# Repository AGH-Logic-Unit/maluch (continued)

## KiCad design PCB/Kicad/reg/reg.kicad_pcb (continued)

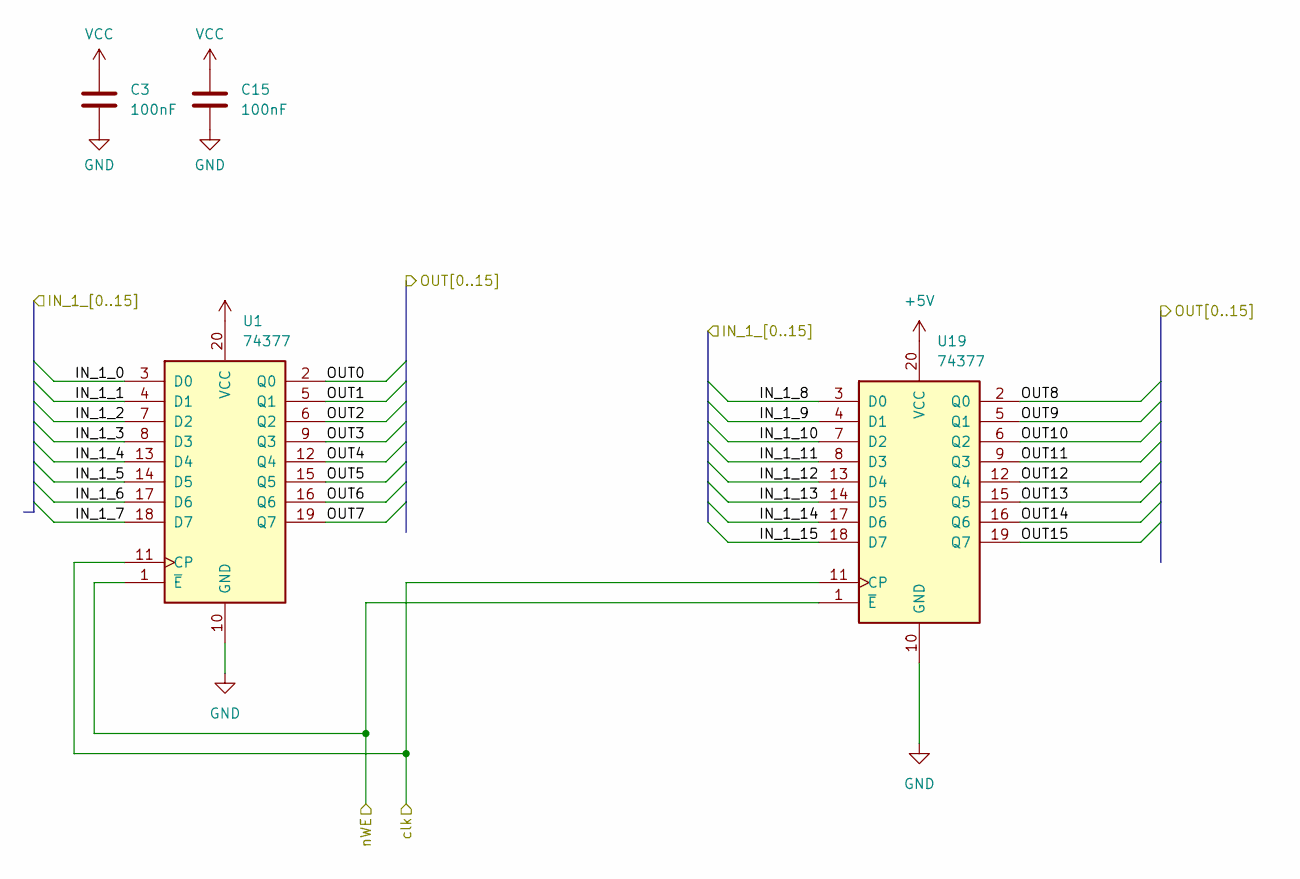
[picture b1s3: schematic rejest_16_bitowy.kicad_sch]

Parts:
C3, C15: 100nF; C_0402_1005Metric
U1, U19: 74377; SSOP-20_5.3x7.2mm_P0.65mm

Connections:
+5V: C3.1, C15.1, U1.20 (VCC), U19.20 (VCC); also elsewhere on the board
/16 bit buffor23/OUT0: U1.3 (D0); also elsewhere on the board
/16 bit buffor23/OUT1: U1.4 (D1); also elsewhere on the board
/16 bit buffor23/OUT2: U1.7 (D2); also elsewhere on the board
/16 bit buffor23/OUT3: U1.8 (D3); also elsewhere on the board
/16 bit buffor23/OUT4: U1.13 (D4); also elsewhere on the board
/16 bit buffor23/OUT5: U1.14 (D5); also elsewhere on the board
/16 bit buffor23/OUT6: U1.17 (D6); also elsewhere on the board
/16 bit buffor23/OUT7: U1.18 (D7); also elsewhere on the board
/16 bit buffor23/OUT8: U19.3 (D0); also elsewhere on the board
/16 bit buffor23/OUT9: U19.4 (D1); also elsewhere on the board
/16 bit buffor23/OUT10: U19.7 (D2); also elsewhere on the board
/16 bit buffor23/OUT11: U19.8 (D3); also elsewhere on the board
/16 bit buffor23/OUT12: U19.13 (D4); also elsewhere on the board
/16 bit buffor23/OUT13: U19.14 (D5); also elsewhere on the board
/16 bit buffor23/OUT14: U19.17 (D6); also elsewhere on the board
/16 bit buffor23/OUT15: U19.18 (D7); also elsewhere on the board
/16 bit register18/nWE: U1.1 (~E), U19.1 (~E); also elsewhere on the board
/clk: U1.11 (CP), U19.11 (CP); also elsewhere on the board
/mask_saved0: U1.2 (Q0); also elsewhere on the board
/mask_saved1: U1.5 (Q1); also elsewhere on the board
/mask_saved2: U1.6 (Q2); also elsewhere on the board
/mask_saved3: U1.9 (Q3); also elsewhere on the board
/mask_saved4: U1.12 (Q4); also elsewhere on the board
/mask_saved5: U1.15 (Q5); also elsewhere on the board
/mask_saved6: U1.16 (Q6); also elsewhere on the board
/mask_saved7: U1.19 (Q7); also elsewhere on the board
/mask_saved8: U19.2 (Q0); also elsewhere on the board
/mask_saved9: U19.5 (Q1); also elsewhere on the board
/mask_saved10: U19.6 (Q2); also elsewhere on the board
/mask_saved11: U19.9 (Q3); also elsewhere on the board
/mask_saved12: U19.12 (Q4); also elsewhere on the board
/mask_saved13: U19.15 (Q5); also elsewhere on the board
/mask_saved14: U19.16 (Q6); also elsewhere on the board
/mask_saved15: U19.19 (Q7); also elsewhere on the board
GND: C3.2, C15.2, U1.10 (GND), U19.10 (GND); also elsewhere on the board

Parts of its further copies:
C4, C16, C17, C18, C19, C20, C21, C22, C23, C24, C25, C26, C27, C28, C29, C30, C31, C32, C33, C34, C35, C36, C37, C38, C39, C40, C41, C42, C43, C44, C45, C46: 100nF; C_0402_1005Metric
U14, U18, U20, U23, U24, U25, U26, U27, U28, U31, U32, U33, U34, U35, U36, U37, U38, U39, U40, U41, U42, U43, U44, U45, U46, U47, U48, U49, U50, U51, U52, U53: 74377; SSOP-20_5.3x7.2mm_P0.65mm

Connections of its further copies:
+5V: C4.1, C16.1, C17.1, C18.1, C19.1, C20.1, C21.1, C22.1, C23.1, C24.1, C25.1, C26.1, C27.1, C28.1, C29.1, C30.1, C31.1, C32.1, C33.1, C34.1, C35.1, C36.1, C37.1, C38.1, C39.1, C40.1, C41.1, C42.1, C43.1, C44.1, C45.1, C46.1, U14.20 (VCC), U18.20 (VCC), U20.20 (VCC), U23.20 (VCC), U24.20 (VCC), U25.20 (VCC), U26.20 (VCC), U27.20 (VCC), U28.20 (VCC), U31.20 (VCC), U32.20 (VCC), U33.20 (VCC), U34.20 (VCC), U35.20 (VCC), U36.20 (VCC), U37.20 (VCC), U38.20 (VCC), U39.20 (VCC), U40.20 (VCC), U41.20 (VCC), U42.20 (VCC), U43.20 (VCC), U44.20 (VCC), U45.20 (VCC), U46.20 (VCC), U47.20 (VCC), U48.20 (VCC), U49.20 (VCC), U50.20 (VCC), U51.20 (VCC), U52.20 (VCC), U53.20 (VCC); also elsewhere on the board
/16 bit buffor25/OUT0: U14.3 (D0); also elsewhere on the board
/16 bit buffor25/OUT1: U14.4 (D1); also elsewhere on the board
/16 bit buffor25/OUT2: U14.7 (D2); also elsewhere on the board
/16 bit buffor25/OUT3: U14.8 (D3); also elsewhere on the board
/16 bit buffor25/OUT4: U14.13 (D4); also elsewhere on the board
/16 bit buffor25/OUT5: U14.14 (D5); also elsewhere on the board
/16 bit buffor25/OUT6: U14.17 (D6); also elsewhere on the board
/16 bit buffor25/OUT7: U14.18 (D7); also elsewhere on the board
/16 bit buffor25/OUT8: U20.3 (D0); also elsewhere on the board
/16 bit buffor25/OUT9: U20.4 (D1); also elsewhere on the board
/16 bit buffor25/OUT10: U20.7 (D2); also elsewhere on the board
/16 bit buffor25/OUT11: U20.8 (D3); also elsewhere on the board
/16 bit buffor25/OUT12: U20.13 (D4); also elsewhere on the board
/16 bit buffor25/OUT13: U20.14 (D5); also elsewhere on the board
/16 bit buffor25/OUT14: U20.17 (D6); also elsewhere on the board
/16 bit buffor25/OUT15: U20.18 (D7); also elsewhere on the board
/16 bit buffor28/IN_1_0: U18.2 (Q0); also elsewhere on the board
/16 bit buffor28/IN_1_1: U18.5 (Q1); also elsewhere on the board
/16 bit buffor28/IN_1_2: U18.6 (Q2); also elsewhere on the board
/16 bit buffor28/IN_1_3: U18.9 (Q3); also elsewhere on the board
/16 bit buffor28/IN_1_4: U18.12 (Q4); also elsewhere on the board
/16 bit buffor28/IN_1_5: U18.15 (Q5); also elsewhere on the board
/16 bit buffor28/IN_1_6: U18.16 (Q6); also elsewhere on the board
/16 bit buffor28/IN_1_7: U18.19 (Q7); also elsewhere on the board
/16 bit buffor28/IN_1_8: U23.2 (Q0); also elsewhere on the board
/16 bit buffor28/IN_1_9: U23.5 (Q1); also elsewhere on the board
/16 bit buffor28/IN_1_10: U23.6 (Q2); also elsewhere on the board
/16 bit buffor28/IN_1_11: U23.9 (Q3); also elsewhere on the board
/16 bit buffor28/IN_1_12: U23.12 (Q4); also elsewhere on the board
/16 bit buffor28/IN_1_13: U23.15 (Q5); also elsewhere on the board
/16 bit buffor28/IN_1_14: U23.16 (Q6); also elsewhere on the board
/16 bit buffor28/IN_1_15: U23.19 (Q7); also elsewhere on the board
/16 bit buffor29/IN_1_0: U31.2 (Q0); also elsewhere on the board
/16 bit buffor29/IN_1_1: U31.5 (Q1); also elsewhere on the board
/16 bit buffor29/IN_1_2: U31.6 (Q2); also elsewhere on the board
/16 bit buffor29/IN_1_3: U31.9 (Q3); also elsewhere on the board
/16 bit buffor29/IN_1_4: U31.12 (Q4); also elsewhere on the board
/16 bit buffor29/IN_1_5: U31.15 (Q5); also elsewhere on the board
/16 bit buffor29/IN_1_6: U31.16 (Q6); also elsewhere on the board
/16 bit buffor29/IN_1_7: U31.19 (Q7); also elsewhere on the board
/16 bit buffor29/IN_1_8: U24.2 (Q0); also elsewhere on the board
/16 bit buffor29/IN_1_9: U24.5 (Q1); also elsewhere on the board
/16 bit buffor29/IN_1_10: U24.6 (Q2); also elsewhere on the board
/16 bit buffor29/IN_1_11: U24.9 (Q3); also elsewhere on the board
/16 bit buffor29/IN_1_12: U24.12 (Q4); also elsewhere on the board
/16 bit buffor29/IN_1_13: U24.15 (Q5); also elsewhere on the board
/16 bit buffor29/IN_1_14: U24.16 (Q6); also elsewhere on the board
/16 bit buffor29/IN_1_15: U24.19 (Q7); also elsewhere on the board
/16 bit buffor30/IN_1_0: U32.2 (Q0); also elsewhere on the board
/16 bit buffor30/IN_1_1: U32.5 (Q1); also elsewhere on the board
/16 bit buffor30/IN_1_2: U32.6 (Q2); also elsewhere on the board
/16 bit buffor30/IN_1_3: U32.9 (Q3); also elsewhere on the board
/16 bit buffor30/IN_1_4: U32.12 (Q4); also elsewhere on the board
/16 bit buffor30/IN_1_5: U32.15 (Q5); also elsewhere on the board
/16 bit buffor30/IN_1_6: U32.16 (Q6); also elsewhere on the board
/16 bit buffor30/IN_1_7: U32.19 (Q7); also elsewhere on the board
/16 bit buffor30/IN_1_8: U25.2 (Q0); also elsewhere on the board
/16 bit buffor30/IN_1_9: U25.5 (Q1); also elsewhere on the board
/16 bit buffor30/IN_1_10: U25.6 (Q2); also elsewhere on the board
/16 bit buffor30/IN_1_11: U25.9 (Q3); also elsewhere on the board
/16 bit buffor30/IN_1_12: U25.12 (Q4); also elsewhere on the board
/16 bit buffor30/IN_1_13: U25.15 (Q5); also elsewhere on the board
/16 bit buffor30/IN_1_14: U25.16 (Q6); also elsewhere on the board
/16 bit buffor30/IN_1_15: U25.19 (Q7); also elsewhere on the board
/16 bit buffor31/IN_1_0: U42.2 (Q0); also elsewhere on the board
/16 bit buffor31/IN_1_1: U42.5 (Q1); also elsewhere on the board
/16 bit buffor31/IN_1_2: U42.6 (Q2); also elsewhere on the board
/16 bit buffor31/IN_1_3: U42.9 (Q3); also elsewhere on the board
/16 bit buffor31/IN_1_4: U42.12 (Q4); also elsewhere on the board
/16 bit buffor31/IN_1_5: U42.15 (Q5); also elsewhere on the board
/16 bit buffor31/IN_1_6: U42.16 (Q6); also elsewhere on the board
/16 bit buffor31/IN_1_7: U42.19 (Q7); also elsewhere on the board
/16 bit buffor31/IN_1_8: U39.2 (Q0); also elsewhere on the board
/16 bit buffor31/IN_1_9: U39.5 (Q1); also elsewhere on the board
/16 bit buffor31/IN_1_10: U39.6 (Q2); also elsewhere on the board
/16 bit buffor31/IN_1_11: U39.9 (Q3); also elsewhere on the board
/16 bit buffor31/IN_1_12: U39.12 (Q4); also elsewhere on the board
/16 bit buffor31/IN_1_13: U39.15 (Q5); also elsewhere on the board
/16 bit buffor31/IN_1_14: U39.16 (Q6); also elsewhere on the board
/16 bit buffor31/IN_1_15: U39.19 (Q7); also elsewhere on the board
/16 bit buffor32/IN_1_0: U33.2 (Q0); also elsewhere on the board
/16 bit buffor32/IN_1_1: U33.5 (Q1); also elsewhere on the board
/16 bit buffor32/IN_1_2: U33.6 (Q2); also elsewhere on the board
/16 bit buffor32/IN_1_3: U33.9 (Q3); also elsewhere on the board
/16 bit buffor32/IN_1_4: U33.12 (Q4); also elsewhere on the board
/16 bit buffor32/IN_1_5: U33.15 (Q5); also elsewhere on the board
/16 bit buffor32/IN_1_6: U33.16 (Q6); also elsewhere on the board
/16 bit buffor32/IN_1_7: U33.19 (Q7); also elsewhere on the board
/16 bit buffor32/IN_1_8: U26.2 (Q0); also elsewhere on the board
/16 bit buffor32/IN_1_9: U26.5 (Q1); also elsewhere on the board
/16 bit buffor32/IN_1_10: U26.6 (Q2); also elsewhere on the board
/16 bit buffor32/IN_1_11: U26.9 (Q3); also elsewhere on the board
/16 bit buffor32/IN_1_12: U26.12 (Q4); also elsewhere on the board
/16 bit buffor32/IN_1_13: U26.15 (Q5); also elsewhere on the board
/16 bit buffor32/IN_1_14: U26.16 (Q6); also elsewhere on the board
/16 bit buffor32/IN_1_15: U26.19 (Q7); also elsewhere on the board
/16 bit buffor33/IN_1_0: U34.2 (Q0); also elsewhere on the board
/16 bit buffor33/IN_1_1: U34.5 (Q1); also elsewhere on the board
/16 bit buffor33/IN_1_2: U34.6 (Q2); also elsewhere on the board
/16 bit buffor33/IN_1_3: U34.9 (Q3); also elsewhere on the board
/16 bit buffor33/IN_1_4: U34.12 (Q4); also elsewhere on the board
/16 bit buffor33/IN_1_5: U34.15 (Q5); also elsewhere on the board
/16 bit buffor33/IN_1_6: U34.16 (Q6); also elsewhere on the board
/16 bit buffor33/IN_1_7: U34.19 (Q7); also elsewhere on the board
/16 bit buffor33/IN_1_8: U27.2 (Q0); also elsewhere on the board
/16 bit buffor33/IN_1_9: U27.5 (Q1); also elsewhere on the board
/16 bit buffor33/IN_1_10: U27.6 (Q2); also elsewhere on the board
/16 bit buffor33/IN_1_11: U27.9 (Q3); also elsewhere on the board
/16 bit buffor33/IN_1_12: U27.12 (Q4); also elsewhere on the board
/16 bit buffor33/IN_1_13: U27.15 (Q5); also elsewhere on the board
/16 bit buffor33/IN_1_14: U27.16 (Q6); also elsewhere on the board
/16 bit buffor33/IN_1_15: U27.19 (Q7); also elsewhere on the board
/16 bit buffor34/IN_1_0: U37.2 (Q0); also elsewhere on the board
/16 bit buffor34/IN_1_1: U37.5 (Q1); also elsewhere on the board
/16 bit buffor34/IN_1_2: U37.6 (Q2); also elsewhere on the board
/16 bit buffor34/IN_1_3: U37.9 (Q3); also elsewhere on the board
/16 bit buffor34/IN_1_4: U37.12 (Q4); also elsewhere on the board
/16 bit buffor34/IN_1_5: U37.15 (Q5); also elsewhere on the board
/16 bit buffor34/IN_1_6: U37.16 (Q6); also elsewhere on the board
/16 bit buffor34/IN_1_7: U37.19 (Q7); also elsewhere on the board
/16 bit buffor34/IN_1_8: U28.2 (Q0); also elsewhere on the board
/16 bit buffor34/IN_1_9: U28.5 (Q1); also elsewhere on the board
/16 bit buffor34/IN_1_10: U28.6 (Q2); also elsewhere on the board
/16 bit buffor34/IN_1_11: U28.9 (Q3); also elsewhere on the board
/16 bit buffor34/IN_1_12: U28.12 (Q4); also elsewhere on the board
/16 bit buffor34/IN_1_13: U28.15 (Q5); also elsewhere on the board
/16 bit buffor34/IN_1_14: U28.16 (Q6); also elsewhere on the board
/16 bit buffor34/IN_1_15: U28.19 (Q7); also elsewhere on the board
/16 bit buffor35/IN_1_0: U38.2 (Q0); also elsewhere on the board
/16 bit buffor35/IN_1_1: U38.5 (Q1); also elsewhere on the board
/16 bit buffor35/IN_1_2: U38.6 (Q2); also elsewhere on the board
/16 bit buffor35/IN_1_3: U38.9 (Q3); also elsewhere on the board
/16 bit buffor35/IN_1_4: U38.12 (Q4); also elsewhere on the board
/16 bit buffor35/IN_1_5: U38.15 (Q5); also elsewhere on the board
/16 bit buffor35/IN_1_6: U38.16 (Q6); also elsewhere on the board
/16 bit buffor35/IN_1_7: U38.19 (Q7); also elsewhere on the board
/16 bit buffor35/IN_1_8: U35.2 (Q0); also elsewhere on the board
/16 bit buffor35/IN_1_9: U35.5 (Q1); also elsewhere on the board
/16 bit buffor35/IN_1_10: U35.6 (Q2); also elsewhere on the board
/16 bit buffor35/IN_1_11: U35.9 (Q3); also elsewhere on the board
/16 bit buffor35/IN_1_12: U35.12 (Q4); also elsewhere on the board
/16 bit buffor35/IN_1_13: U35.15 (Q5); also elsewhere on the board
/16 bit buffor35/IN_1_14: U35.16 (Q6); also elsewhere on the board
/16 bit buffor35/IN_1_15: U35.19 (Q7); also elsewhere on the board
/16 bit buffor36/IN_1_0: U41.2 (Q0); also elsewhere on the board
/16 bit buffor36/IN_1_1: U41.5 (Q1); also elsewhere on the board
/16 bit buffor36/IN_1_2: U41.6 (Q2); also elsewhere on the board
/16 bit buffor36/IN_1_3: U41.9 (Q3); also elsewhere on the board
/16 bit buffor36/IN_1_4: U41.12 (Q4); also elsewhere on the board
/16 bit buffor36/IN_1_5: U41.15 (Q5); also elsewhere on the board
/16 bit buffor36/IN_1_6: U41.16 (Q6); also elsewhere on the board
/16 bit buffor36/IN_1_7: U41.19 (Q7); also elsewhere on the board
/16 bit buffor36/IN_1_8: U36.2 (Q0); also elsewhere on the board
/16 bit buffor36/IN_1_9: U36.5 (Q1); also elsewhere on the board
/16 bit buffor36/IN_1_10: U36.6 (Q2); also elsewhere on the board
/16 bit buffor36/IN_1_11: U36.9 (Q3); also elsewhere on the board
/16 bit buffor36/IN_1_12: U36.12 (Q4); also elsewhere on the board
/16 bit buffor36/IN_1_13: U36.15 (Q5); also elsewhere on the board
/16 bit buffor36/IN_1_14: U36.16 (Q6); also elsewhere on the board
/16 bit buffor36/IN_1_15: U36.19 (Q7); also elsewhere on the board
/16 bit buffor37/IN_1_0: U45.2 (Q0); also elsewhere on the board
/16 bit buffor37/IN_1_1: U45.5 (Q1); also elsewhere on the board
/16 bit buffor37/IN_1_2: U45.6 (Q2); also elsewhere on the board
/16 bit buffor37/IN_1_3: U45.9 (Q3); also elsewhere on the board
/16 bit buffor37/IN_1_4: U45.12 (Q4); also elsewhere on the board
/16 bit buffor37/IN_1_5: U45.15 (Q5); also elsewhere on the board
/16 bit buffor37/IN_1_6: U45.16 (Q6); also elsewhere on the board
/16 bit buffor37/IN_1_7: U45.19 (Q7); also elsewhere on the board
/16 bit buffor37/IN_1_8: U40.2 (Q0); also elsewhere on the board
/16 bit buffor37/IN_1_9: U40.5 (Q1); also elsewhere on the board
/16 bit buffor37/IN_1_10: U40.6 (Q2); also elsewhere on the board
/16 bit buffor37/IN_1_11: U40.9 (Q3); also elsewhere on the board
/16 bit buffor37/IN_1_12: U40.12 (Q4); also elsewhere on the board
/16 bit buffor37/IN_1_13: U40.15 (Q5); also elsewhere on the board
/16 bit buffor37/IN_1_14: U40.16 (Q6); also elsewhere on the board
/16 bit buffor37/IN_1_15: U40.19 (Q7); also elsewhere on the board
/16 bit buffor38/IN_1_0: U46.2 (Q0); also elsewhere on the board
/16 bit buffor38/IN_1_1: U46.5 (Q1); also elsewhere on the board
/16 bit buffor38/IN_1_2: U46.6 (Q2); also elsewhere on the board
/16 bit buffor38/IN_1_3: U46.9 (Q3); also elsewhere on the board
/16 bit buffor38/IN_1_4: U46.12 (Q4); also elsewhere on the board
/16 bit buffor38/IN_1_5: U46.15 (Q5); also elsewhere on the board
/16 bit buffor38/IN_1_6: U46.16 (Q6); also elsewhere on the board
/16 bit buffor38/IN_1_7: U46.19 (Q7); also elsewhere on the board
/16 bit buffor38/IN_1_8: U43.2 (Q0); also elsewhere on the board
/16 bit buffor38/IN_1_9: U43.5 (Q1); also elsewhere on the board
/16 bit buffor38/IN_1_10: U43.6 (Q2); also elsewhere on the board
/16 bit buffor38/IN_1_11: U43.9 (Q3); also elsewhere on the board
/16 bit buffor38/IN_1_12: U43.12 (Q4); also elsewhere on the board
/16 bit buffor38/IN_1_13: U43.15 (Q5); also elsewhere on the board
/16 bit buffor38/IN_1_14: U43.16 (Q6); also elsewhere on the board
/16 bit buffor38/IN_1_15: U43.19 (Q7); also elsewhere on the board
/16 bit buffor39/IN_1_0: U50.2 (Q0); also elsewhere on the board
/16 bit buffor39/IN_1_1: U50.5 (Q1); also elsewhere on the board
/16 bit buffor39/IN_1_2: U50.6 (Q2); also elsewhere on the board
/16 bit buffor39/IN_1_3: U50.9 (Q3); also elsewhere on the board
/16 bit buffor39/IN_1_4: U50.12 (Q4); also elsewhere on the board
/16 bit buffor39/IN_1_5: U50.15 (Q5); also elsewhere on the board
/16 bit buffor39/IN_1_6: U50.16 (Q6); also elsewhere on the board
/16 bit buffor39/IN_1_7: U50.19 (Q7); also elsewhere on the board
/16 bit buffor39/IN_1_8: U47.2 (Q0); also elsewhere on the board
/16 bit buffor39/IN_1_9: U47.5 (Q1); also elsewhere on the board
/16 bit buffor39/IN_1_10: U47.6 (Q2); also elsewhere on the board
/16 bit buffor39/IN_1_11: U47.9 (Q3); also elsewhere on the board
/16 bit buffor39/IN_1_12: U47.12 (Q4); also elsewhere on the board
/16 bit buffor39/IN_1_13: U47.15 (Q5); also elsewhere on the board
/16 bit buffor39/IN_1_14: U47.16 (Q6); also elsewhere on the board
/16 bit buffor39/IN_1_15: U47.19 (Q7); also elsewhere on the board
/16 bit buffor40/IN_1_0: U49.2 (Q0); also elsewhere on the board
/16 bit buffor40/IN_1_1: U49.5 (Q1); also elsewhere on the board
/16 bit buffor40/IN_1_2: U49.6 (Q2); also elsewhere on the board
/16 bit buffor40/IN_1_3: U49.9 (Q3); also elsewhere on the board
/16 bit buffor40/IN_1_4: U49.12 (Q4); also elsewhere on the board
/16 bit buffor40/IN_1_5: U49.15 (Q5); also elsewhere on the board
/16 bit buffor40/IN_1_6: U49.16 (Q6); also elsewhere on the board
/16 bit buffor40/IN_1_7: U49.19 (Q7); also elsewhere on the board
/16 bit buffor40/IN_1_8: U44.2 (Q0); also elsewhere on the board
/16 bit buffor40/IN_1_9: U44.5 (Q1); also elsewhere on the board
/16 bit buffor40/IN_1_10: U44.6 (Q2); also elsewhere on the board
/16 bit buffor40/IN_1_11: U44.9 (Q3); also elsewhere on the board
/16 bit buffor40/IN_1_12: U44.12 (Q4); also elsewhere on the board
/16 bit buffor40/IN_1_13: U44.15 (Q5); also elsewhere on the board
/16 bit buffor40/IN_1_14: U44.16 (Q6); also elsewhere on the board
/16 bit buffor40/IN_1_15: U44.19 (Q7); also elsewhere on the board
/16 bit buffor41/IN_1_0: U52.2 (Q0); also elsewhere on the board
/16 bit buffor41/IN_1_1: U52.5 (Q1); also elsewhere on the board
/16 bit buffor41/IN_1_2: U52.6 (Q2); also elsewhere on the board
/16 bit buffor41/IN_1_3: U52.9 (Q3); also elsewhere on the board
/16 bit buffor41/IN_1_4: U52.12 (Q4); also elsewhere on the board
/16 bit buffor41/IN_1_5: U52.15 (Q5); also elsewhere on the board
/16 bit buffor41/IN_1_6: U52.16 (Q6); also elsewhere on the board
/16 bit buffor41/IN_1_7: U52.19 (Q7); also elsewhere on the board
/16 bit buffor41/IN_1_8: U48.2 (Q0); also elsewhere on the board
/16 bit buffor41/IN_1_9: U48.5 (Q1); also elsewhere on the board
/16 bit buffor41/IN_1_10: U48.6 (Q2); also elsewhere on the board
/16 bit buffor41/IN_1_11: U48.9 (Q3); also elsewhere on the board
/16 bit buffor41/IN_1_12: U48.12 (Q4); also elsewhere on the board
/16 bit buffor41/IN_1_13: U48.15 (Q5); also elsewhere on the board
/16 bit buffor41/IN_1_14: U48.16 (Q6); also elsewhere on the board
/16 bit buffor41/IN_1_15: U48.19 (Q7); also elsewhere on the board
/16 bit register17/nWE: U14.1 (~E), U20.1 (~E); also elsewhere on the board
/IO0: U53.3 (D0); also elsewhere on the board
/IO1: U53.4 (D1); also elsewhere on the board
/IO2: U53.7 (D2); also elsewhere on the board
/IO3: U53.8 (D3); also elsewhere on the board
/IO4: U53.13 (D4); also elsewhere on the board
/IO5: U53.14 (D5); also elsewhere on the board
/IO6: U53.17 (D6); also elsewhere on the board
/IO7: U53.18 (D7); also elsewhere on the board
/IO8: U51.3 (D0); also elsewhere on the board
/IO9: U51.4 (D1); also elsewhere on the board
/IO10: U51.7 (D2); also elsewhere on the board
/IO11: U51.8 (D3); also elsewhere on the board
/IO12: U51.13 (D4); also elsewhere on the board
/IO13: U51.14 (D5); also elsewhere on the board
/IO14: U51.17 (D6); also elsewhere on the board
/IO15: U51.18 (D7); also elsewhere on the board
/OUT_1_2: U18.1 (~E), U23.1 (~E); also elsewhere on the board
/OUT_1_3: U24.1 (~E), U31.1 (~E); also elsewhere on the board
/OUT_1_4: U25.1 (~E), U32.1 (~E); also elsewhere on the board
/OUT_1_5: U39.1 (~E), U42.1 (~E); also elsewhere on the board
/OUT_1_6: U26.1 (~E), U33.1 (~E); also elsewhere on the board
/OUT_1_7: U27.1 (~E), U34.1 (~E); also elsewhere on the board
/OUT_1_8: U28.1 (~E), U37.1 (~E); also elsewhere on the board
/OUT_1_9: U35.1 (~E), U38.1 (~E); also elsewhere on the board
/OUT_1_10: U36.1 (~E), U41.1 (~E); also elsewhere on the board
/OUT_1_11: U40.1 (~E), U45.1 (~E); also elsewhere on the board
/OUT_1_12: U43.1 (~E), U46.1 (~E); also elsewhere on the board
/OUT_1_13: U44.1 (~E), U49.1 (~E); also elsewhere on the board
/OUT_1_14: U47.1 (~E), U50.1 (~E); also elsewhere on the board
/OUT_1_15: U48.1 (~E), U52.1 (~E); also elsewhere on the board
/OUT_5_0: U53.2 (Q0); also elsewhere on the board
/OUT_5_1: U53.5 (Q1); also elsewhere on the board
/OUT_5_2: U53.6 (Q2); also elsewhere on the board
/OUT_5_3: U53.9 (Q3); also elsewhere on the board
/OUT_5_4: U53.12 (Q4); also elsewhere on the board
/OUT_5_5: U53.15 (Q5); also elsewhere on the board
/OUT_5_6: U53.16 (Q6); also elsewhere on the board
/OUT_5_7: U53.19 (Q7); also elsewhere on the board
/OUT_5_8: U51.2 (Q0); also elsewhere on the board
/OUT_5_9: U51.5 (Q1); also elsewhere on the board
/OUT_5_10: U51.6 (Q2); also elsewhere on the board
/OUT_5_11: U51.9 (Q3); also elsewhere on the board
/OUT_5_12: U51.12 (Q4); also elsewhere on the board
/OUT_5_13: U51.15 (Q5); also elsewhere on the board
/OUT_5_14: U51.16 (Q6); also elsewhere on the board
/OUT_5_15: U51.19 (Q7); also elsewhere on the board
/clk: U14.11 (CP), U18.11 (CP), U20.11 (CP), U23.11 (CP), U24.11 (CP), U25.11 (CP), U26.11 (CP), U27.11 (CP), U28.11 (CP), U31.11 (CP), U32.11 (CP), U33.11 (CP), U34.11 (CP), U35.11 (CP), U36.11 (CP), U37.11 (CP), U38.11 (CP), U39.11 (CP), U40.11 (CP), U41.11 (CP), U42.11 (CP), U43.11 (CP), U44.11 (CP), U45.11 (CP), U46.11 (CP), U47.11 (CP), U48.11 (CP), U49.11 (CP), U50.11 (CP), U51.11 (CP), U52.11 (CP), U53.11 (CP); also elsewhere on the board
/data0: U18.3 (D0), U31.3 (D0), U32.3 (D0), U33.3 (D0), U34.3 (D0), U37.3 (D0), U38.3 (D0), U41.3 (D0), U42.3 (D0), U45.3 (D0), U46.3 (D0), U49.3 (D0), U50.3 (D0), U52.3 (D0); also elsewhere on the board
/data1: U18.4 (D1), U31.4 (D1), U32.4 (D1), U33.4 (D1), U34.4 (D1), U37.4 (D1), U38.4 (D1), U41.4 (D1), U42.4 (D1), U45.4 (D1), U46.4 (D1), U49.4 (D1), U50.4 (D1), U52.4 (D1); also elsewhere on the board
/data2: U18.7 (D2), U31.7 (D2), U32.7 (D2), U33.7 (D2), U34.7 (D2), U37.7 (D2), U38.7 (D2), U41.7 (D2), U42.7 (D2), U45.7 (D2), U46.7 (D2), U49.7 (D2), U50.7 (D2), U52.7 (D2); also elsewhere on the board
/data3: U18.8 (D3), U31.8 (D3), U32.8 (D3), U33.8 (D3), U34.8 (D3), U37.8 (D3), U38.8 (D3), U41.8 (D3), U42.8 (D3), U45.8 (D3), U46.8 (D3), U49.8 (D3), U50.8 (D3), U52.8 (D3); also elsewhere on the board
/data4: U18.13 (D4), U31.13 (D4), U32.13 (D4), U33.13 (D4), U34.13 (D4), U37.13 (D4), U38.13 (D4), U41.13 (D4), U42.13 (D4), U45.13 (D4), U46.13 (D4), U49.13 (D4), U50.13 (D4), U52.13 (D4); also elsewhere on the board
/data5: U18.14 (D5), U31.14 (D5), U32.14 (D5), U33.14 (D5), U34.14 (D5), U37.14 (D5), U38.14 (D5), U41.14 (D5), U42.14 (D5), U45.14 (D5), U46.14 (D5), U49.14 (D5), U50.14 (D5), U52.14 (D5); also elsewhere on the board
/data6: U18.17 (D6), U31.17 (D6), U32.17 (D6), U33.17 (D6), U34.17 (D6), U37.17 (D6), U38.17 (D6), U41.17 (D6), U42.17 (D6), U45.17 (D6), U46.17 (D6), U49.17 (D6), U50.17 (D6), U52.17 (D6); also elsewhere on the board
/data7: U18.18 (D7), U31.18 (D7), U32.18 (D7), U33.18 (D7), U34.18 (D7), U37.18 (D7), U38.18 (D7), U41.18 (D7), U42.18 (D7), U45.18 (D7), U46.18 (D7), U49.18 (D7), U50.18 (D7), U52.18 (D7); also elsewhere on the board
/data8: U23.3 (D0), U24.3 (D0), U25.3 (D0), U26.3 (D0), U27.3 (D0), U28.3 (D0), U35.3 (D0), U36.3 (D0), U39.3 (D0), U40.3 (D0), U43.3 (D0), U44.3 (D0), U47.3 (D0), U48.3 (D0); also elsewhere on the board
/data9: U23.4 (D1), U24.4 (D1), U25.4 (D1), U26.4 (D1), U27.4 (D1), U28.4 (D1), U35.4 (D1), U36.4 (D1), U39.4 (D1), U40.4 (D1), U43.4 (D1), U44.4 (D1), U47.4 (D1), U48.4 (D1); also elsewhere on the board
/data10: U23.7 (D2), U24.7 (D2), U25.7 (D2), U26.7 (D2), U27.7 (D2), U28.7 (D2), U35.7 (D2), U36.7 (D2), U39.7 (D2), U40.7 (D2), U43.7 (D2), U44.7 (D2), U47.7 (D2), U48.7 (D2); also elsewhere on the board
/data11: U23.8 (D3), U24.8 (D3), U25.8 (D3), U26.8 (D3), U27.8 (D3), U28.8 (D3), U35.8 (D3), U36.8 (D3), U39.8 (D3), U40.8 (D3), U43.8 (D3), U44.8 (D3), U47.8 (D3), U48.8 (D3); also elsewhere on the board
/data12: U23.13 (D4), U24.13 (D4), U25.13 (D4), U26.13 (D4), U27.13 (D4), U28.13 (D4), U35.13 (D4), U36.13 (D4), U39.13 (D4), U40.13 (D4), U43.13 (D4), U44.13 (D4), U47.13 (D4), U48.13 (D4); also elsewhere on the board
/data13: U23.14 (D5), U24.14 (D5), U25.14 (D5), U26.14 (D5), U27.14 (D5), U28.14 (D5), U35.14 (D5), U36.14 (D5), U39.14 (D5), U40.14 (D5), U43.14 (D5), U44.14 (D5), U47.14 (D5), U48.14 (D5); also elsewhere on the board
/data14: U23.17 (D6), U24.17 (D6), U25.17 (D6), U26.17 (D6), U27.17 (D6), U28.17 (D6), U35.17 (D6), U36.17 (D6), U39.17 (D6), U40.17 (D6), U43.17 (D6), U44.17 (D6), U47.17 (D6), U48.17 (D6); also elsewhere on the board
/data15: U23.18 (D7), U24.18 (D7), U25.18 (D7), U26.18 (D7), U27.18 (D7), U28.18 (D7), U35.18 (D7), U36.18 (D7), U39.18 (D7), U40.18 (D7), U43.18 (D7), U44.18 (D7), U47.18 (D7), U48.18 (D7); also elsewhere on the board
/r1_out0: U14.2 (Q0); also elsewhere on the board
/r1_out1: U14.5 (Q1); also elsewhere on the board
/r1_out2: U14.6 (Q2); also elsewhere on the board
/r1_out3: U14.9 (Q3); also elsewhere on the board
/r1_out4: U14.12 (Q4); also elsewhere on the board
/r1_out5: U14.15 (Q5); also elsewhere on the board
/r1_out6: U14.16 (Q6); also elsewhere on the board
/r1_out7: U14.19 (Q7); also elsewhere on the board
/r1_out8: U20.2 (Q0); also elsewhere on the board
/r1_out9: U20.5 (Q1); also elsewhere on the board
/r1_out10: U20.6 (Q2); also elsewhere on the board
/r1_out11: U20.9 (Q3); also elsewhere on the board
/r1_out12: U20.12 (Q4); also elsewhere on the board
/r1_out13: U20.15 (Q5); also elsewhere on the board
/r1_out14: U20.16 (Q6); also elsewhere on the board
/r1_out15: U20.19 (Q7); also elsewhere on the board
GND: C4.2, C16.2, C17.2, C18.2, C19.2, C20.2, C21.2, C22.2, C23.2, C24.2, C25.2, C26.2, C27.2, C28.2, C29.2, C30.2, C31.2, C32.2, C33.2, C34.2, C35.2, C36.2, C37.2, C38.2, C39.2, C40.2, C41.2, C42.2, C43.2, C44.2, C45.2, C46.2, U14.10 (GND), U18.10 (GND), U20.10 (GND), U23.10 (GND), U24.10 (GND), U25.10 (GND), U26.10 (GND), U27.10 (GND), U28.10 (GND), U31.10 (GND), U32.10 (GND), U33.10 (GND), U34.10 (GND), U35.10 (GND), U36.10 (GND), U37.10 (GND), U38.10 (GND), U39.10 (GND), U40.10 (GND), U41.10 (GND), U42.10 (GND), U43.10 (GND), U44.10 (GND), U45.10 (GND), U46.10 (GND), U47.10 (GND), U48.10 (GND), U49.10 (GND), U50.10 (GND), U51.1 (~E), U51.10 (GND), U52.10 (GND), U53.1 (~E), U53.10 (GND); also elsewhere on the board
